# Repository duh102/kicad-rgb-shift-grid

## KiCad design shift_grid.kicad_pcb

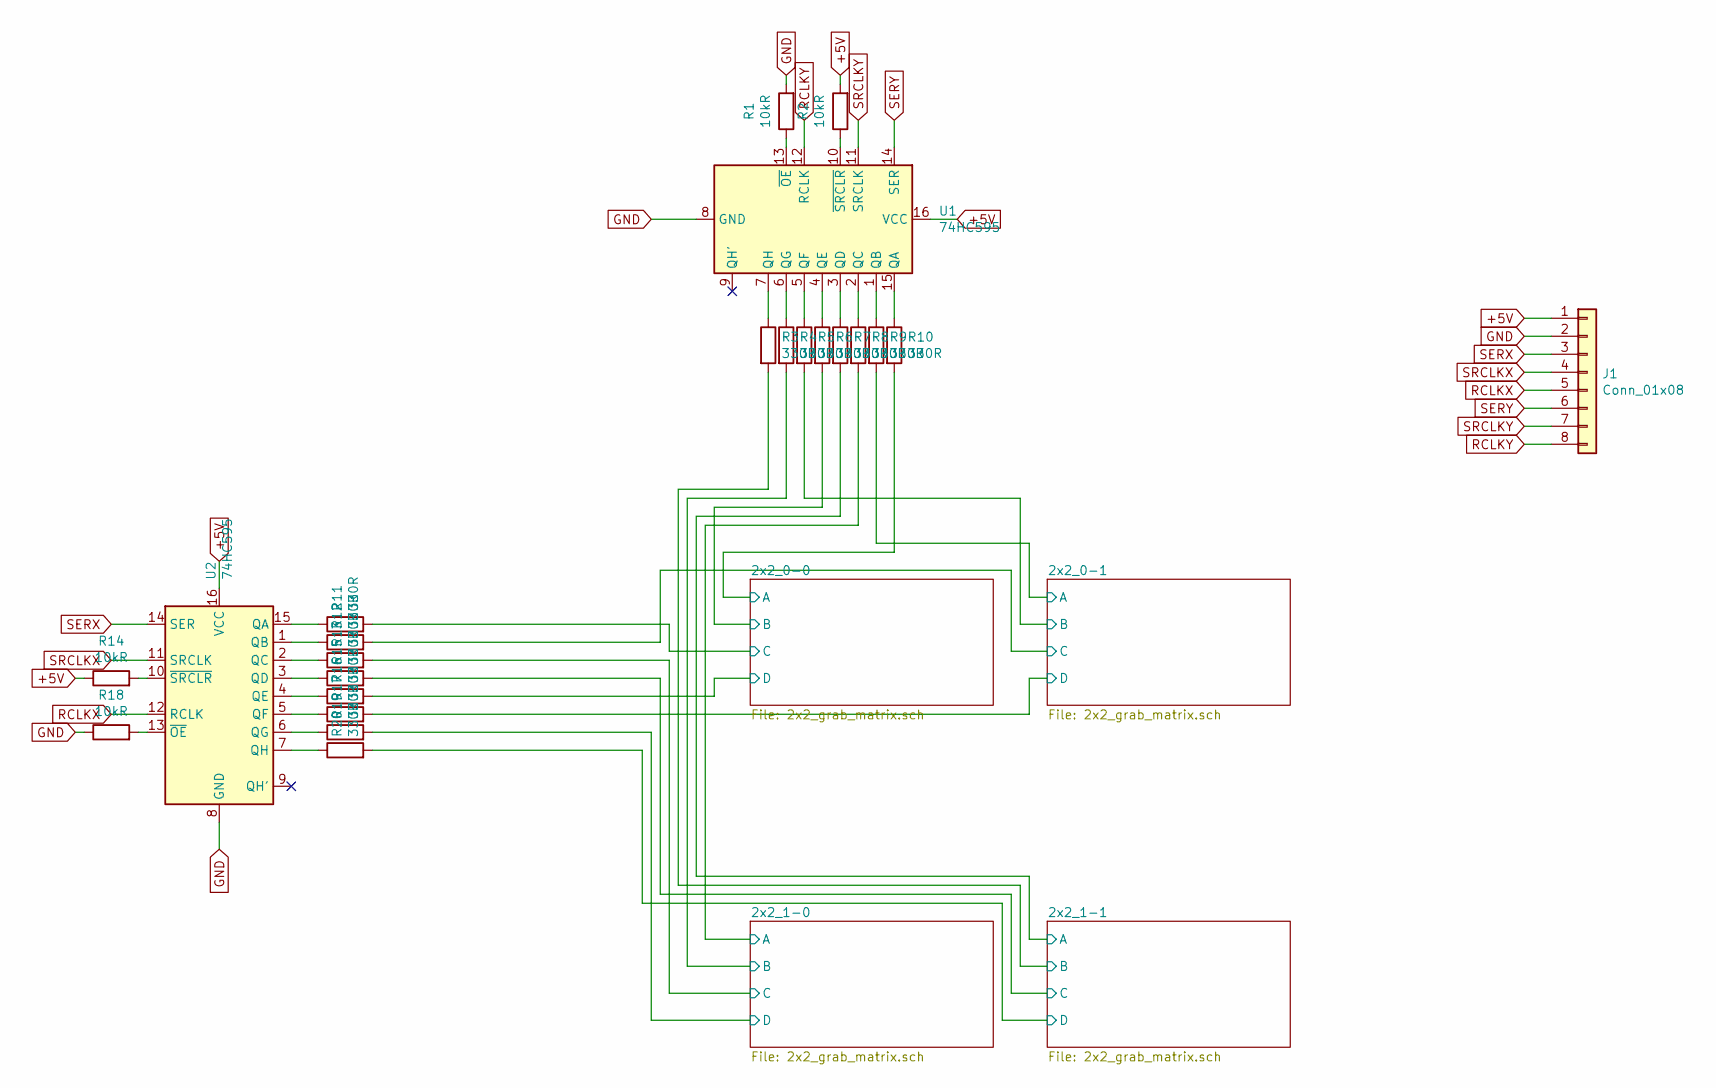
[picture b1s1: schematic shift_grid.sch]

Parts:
J1: Conn_01x08; PinHeader_1x08_P2.54mm_Vertical
R1, R2, R14, R18: 10kR; R_0805_2012Metric
R3, R4, R5, R6, R7, R8, R9, R10, R11, R12, R13, R15, R16, R17, R19, R20: 330R; R_0805_2012Metric
U1, U2: 74HC595; SOIC-16_3.9x9.9mm_P1.27mm

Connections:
+5V: J1.1, R2.2, R14.1, U1.16 (VCC), U2.16 (VCC)
/2x2_0-0/A: R10.2; also elsewhere on the board
/2x2_0-0/B: R6.2; also elsewhere on the board
/2x2_0-0/C: R11.2; also elsewhere on the board
/2x2_0-0/D: R16.2; also elsewhere on the board
/2x2_0-1/A: R9.2; also elsewhere on the board
/2x2_0-1/B: R5.2; also elsewhere on the board
/2x2_0-1/C: R12.2; also elsewhere on the board
/2x2_0-1/D: R17.2; also elsewhere on the board
/2x2_1-0/A: R8.2; also elsewhere on the board
/2x2_1-0/B: R4.2; also elsewhere on the board
/2x2_1-0/C: R13.2; also elsewhere on the board
/2x2_1-0/D: R19.2; also elsewhere on the board
/2x2_1-1/A: R7.2; also elsewhere on the board
/2x2_1-1/B: R3.2; also elsewhere on the board
/2x2_1-1/C: R15.2; also elsewhere on the board
/2x2_1-1/D: R20.2; also elsewhere on the board
GND: J1.2, R1.2, R18.1, U1.8 (GND), U2.8 (GND)
unnamed: R1.1, U1.13 (~OE)
unnamed: R2.1, U1.10 (~SRCLR)
unnamed: R3.1, U1.7 (QH)
unnamed: R4.1, U1.6 (QG)
unnamed: R5.1, U1.5 (QF)
unnamed: R6.1, U1.4 (QE)
unnamed: R7.1, U1.3 (QD)
unnamed: R8.1, U1.2 (QC)
unnamed: R9.1, U1.1 (QB)
unnamed: R10.1, U1.15 (QA)
unnamed: R11.1, U2.15 (QA)
unnamed: R12.1, U2.1 (QB)
unnamed: R13.1, U2.2 (QC)
unnamed: R14.2, U2.10 (~SRCLR)
unnamed: R15.1, U2.3 (QD)
unnamed: R16.1, U2.4 (QE)
unnamed: R17.1, U2.5 (QF)
unnamed: R18.2, U2.13 (~OE)
unnamed: R19.1, U2.6 (QG)
unnamed: R20.1, U2.7 (QH)
RCLKX: J1.5, U2.12 (RCLK)
RCLKY: J1.8, U1.12 (RCLK)
SERX: J1.3, U2.14 (SER)
SERY: J1.6, U1.14 (SER)
SRCLKX: J1.4, U2.11 (SRCLK)
SRCLKY: J1.7, U1.11 (SRCLK)

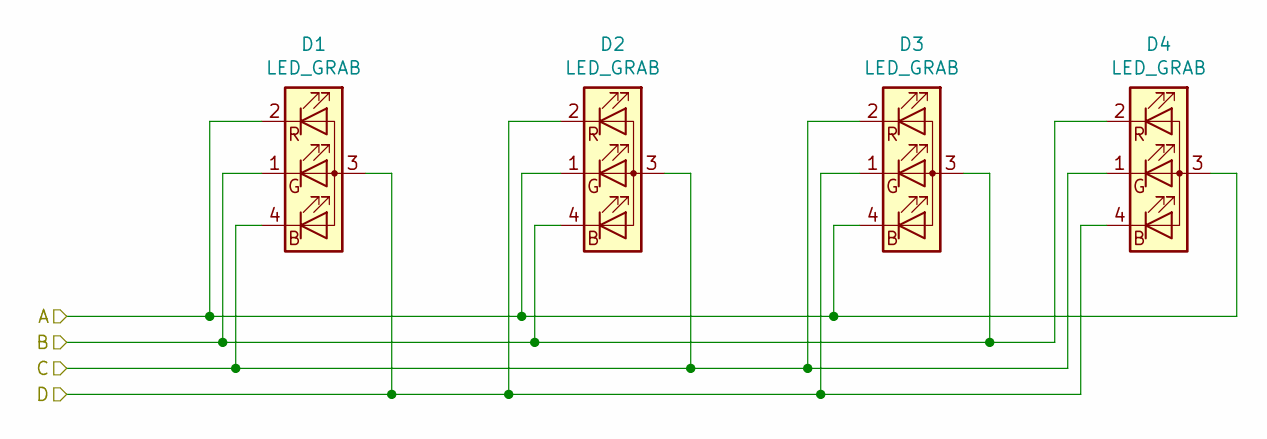
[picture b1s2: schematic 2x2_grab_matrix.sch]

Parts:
D1, D2, D3, D4: LED_GRAB; LED_RGB_Songxin_1615GRAB

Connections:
/2x2_0-0/A: D1.2 (RK), D2.1 (GK), D3.4 (BK), D4.3 (A); also elsewhere on the board
/2x2_0-0/B: D1.1 (GK), D2.4 (BK), D3.3 (A), D4.2 (RK); also elsewhere on the board
/2x2_0-0/C: D1.4 (BK), D2.3 (A), D3.2 (RK), D4.1 (GK); also elsewhere on the board
/2x2_0-0/D: D1.3 (A), D2.2 (RK), D3.1 (GK), D4.4 (BK); also elsewhere on the board

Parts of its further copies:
D5, D6, D7, D8, D9, D10, D11, D12, D13, D14, D15, D16: LED_GRAB; LED_RGB_Songxin_1615GRAB

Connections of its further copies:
/2x2_0-1/A: D9.2 (RK), D10.1 (GK), D11.4 (BK), D12.3 (A); also elsewhere on the board
/2x2_0-1/B: D9.1 (GK), D10.4 (BK), D11.3 (A), D12.2 (RK); also elsewhere on the board
/2x2_0-1/C: D9.4 (BK), D10.3 (A), D11.2 (RK), D12.1 (GK); also elsewhere on the board
/2x2_0-1/D: D9.3 (A), D10.2 (RK), D11.1 (GK), D12.4 (BK); also elsewhere on the board
/2x2_1-0/A: D5.2 (RK), D6.1 (GK), D7.4 (BK), D8.3 (A); also elsewhere on the board
/2x2_1-0/B: D5.1 (GK), D6.4 (BK), D7.3 (A), D8.2 (RK); also elsewhere on the board
/2x2_1-0/C: D5.4 (BK), D6.3 (A), D7.2 (RK), D8.1 (GK); also elsewhere on the board
/2x2_1-0/D: D5.3 (A), D6.2 (RK), D7.1 (GK), D8.4 (BK); also elsewhere on the board
/2x2_1-1/A: D13.2 (RK), D14.1 (GK), D15.4 (BK), D16.3 (A); also elsewhere on the board
/2x2_1-1/B: D13.1 (GK), D14.4 (BK), D15.3 (A), D16.2 (RK); also elsewhere on the board
/2x2_1-1/C: D13.4 (BK), D14.3 (A), D15.2 (RK), D16.1 (GK); also elsewhere on the board
/2x2_1-1/D: D13.3 (A), D14.2 (RK), D15.1 (GK), D16.4 (BK); also elsewhere on the board

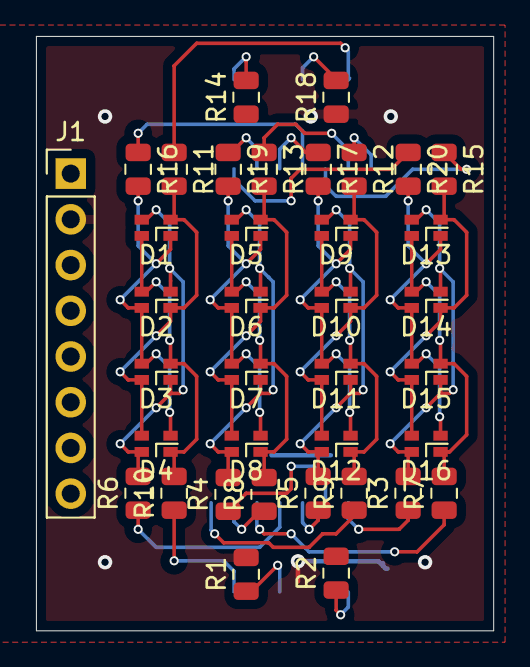
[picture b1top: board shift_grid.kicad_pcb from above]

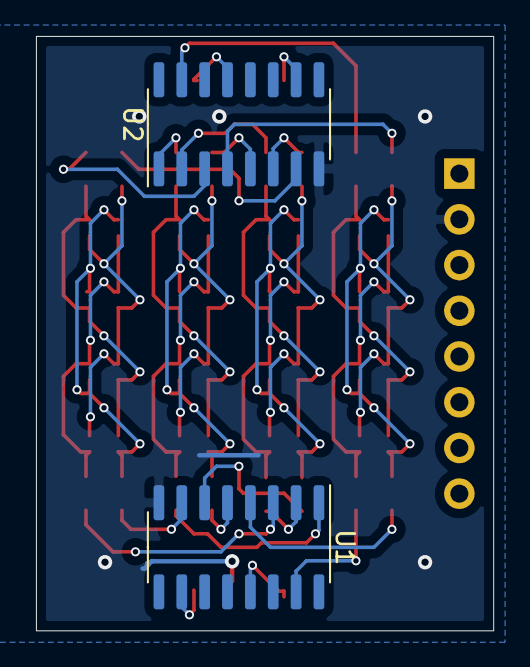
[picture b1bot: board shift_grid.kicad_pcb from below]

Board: 2 copper layers, 25.4 x 33.0 mm, 39 parts (2 on the bottom side), 44 nets.
